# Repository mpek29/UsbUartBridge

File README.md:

# UsbUartBridge

## 🚀 Overview

**UsbUartBridge** is an open-source PCB designed to provide a **USB-to-UART bridge** for seamless serial communication between a computer and microcontrollers. The board features **JST-SH & JST-PH connectors** for easy integration into embedded projects, IoT devices, and prototyping setups.

## 🎯 Purpose

- 🔌 **Reliable USB-to-Serial Conversion**: Enables communication between a PC and embedded systems via UART.
- 📏 **Compact and Adafruit-compatible**: Designed to fit within Adafruit's standard PCB footprint.
- 🛠️ **Open-source and customizable**: Modify and adapt the design to suit your specific needs.

## 📝 Features

| 🏷️ Feature            | 🔍 Description                                                                           |
| ---------------------- | ---------------------------------------------------------------------------------------- |
| 🔌 **USB Interface**   | Micro-USB (for PC connection)                                                            |
| 📡 **UART Interface**  | TX, RX, DTR                                                                              |
| 🔋 **Voltage Options** | 3.3V & 5V selectable output                                                              |
| 🛠️ **Connectivity**   | JST-SH & JST-PH connectors for easy integration                                          |
| 🔧 **Capacitors**      | Decoupling capacitors for stability                                                      |
| 🖥️ **PCB Design**     | Open-source & customizable                                                               |
| 🌍 **Use Cases**       | Debugging & Programming microcontrollers, IoT device communication, serial data transfer |

## 📐 PCB Design Preview
| 📜 Schematic | 🖥️ PCB Layout | 🏗️ 3D |
|-----------|-----------|-----------|
|  |  |  |

## 🌟 License

This project is open-source. Feel free to use, modify, and contribute! 🚀

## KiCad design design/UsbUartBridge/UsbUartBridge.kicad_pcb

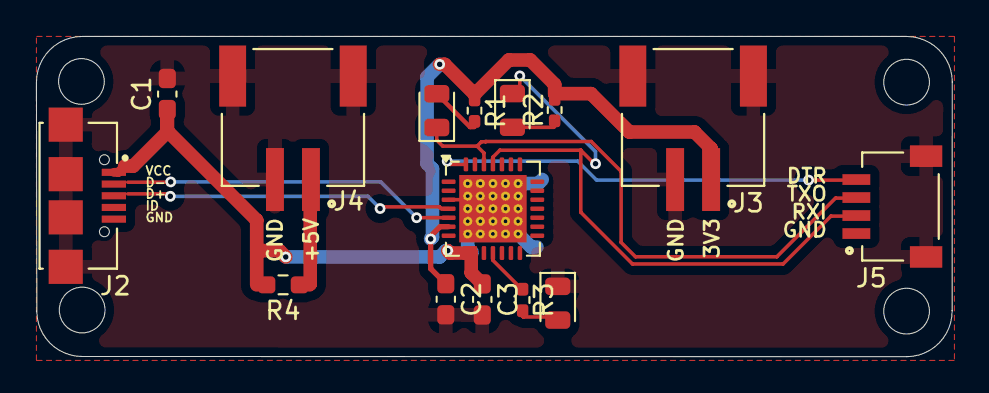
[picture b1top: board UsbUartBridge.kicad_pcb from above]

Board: 2 copper layers, 50.9 x 17.8 mm, 15 parts (0 on the bottom side), 13 nets.

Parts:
C1, C2, C3: 100nF; C_0603_1608Metric_Pad1.08x0.95mm_HandSolder
D1, D2, D3: LED; LED_0805_2012Metric
J2: UJ2-MIBH-G-SMT-TR; CUI_UJ2-MIBH-G-SMT-TR
J3, J4: S2B-PH-SM4-TB_LF__SN_; JST_S2B-PH-SM4-TB_LF__SN_
J5: SM04B-SRSS-TB_LF__SN_; JST_SM04B-SRSS-TB_LF__SN_
R1, R2, R3: 1k; R_0402_1005Metric_Pad0.72x0.64mm_HandSolder
R4: 470; R_0603_1608Metric_Pad0.98x0.95mm_HandSolder
U1: CP2102; QFN-28-1EP_5x5mm_P0.5mm_EP3.75x3.75mm_ThermalVias

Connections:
+5V: J4.1, R4.1
D+: J2.3 (D+), U1.4 (D+)
D-: J2.2 (D-), U1.5 (D-)
DTR: J5.1, U1.28 (DTR)
GND: C1.2, C2.2, C3.2, D3.1 (K), J2.5 (GND), J3.2, J3.S1 (SHIELD), J3.S2 (SHIELD), J4.2, J4.S1 (SHIELD), J4.S2 (SHIELD), J5.4, J5.S1 (SHIELD), J5.S2 (SHIELD), U1.3 (GND), U1.29 (GND)
unnamed: D1.2 (A), R1.2
unnamed: D2.2 (A), R2.1
unnamed: D3.2 (A), R3.2
RXI: D2.1 (K), J5.2, U1.25 (RXD)
TXO: D1.1 (K), J5.3, U1.26 (TXD)
VCC: C1.1, C3.1, J2.1 (VCC), R4.2, U1.8 (VBUS), U1.9 (~RST)
VDD: C2.1, J3.1, R1.1, R2.2, U1.6 (VDD)
~SUSPEND: R3.1, U1.11 (~SUSPEND)

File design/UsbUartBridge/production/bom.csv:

Designator,Footprint,Quantity,Value,LCSC Part #
"C1, C2, C3",0603,3,100nF,
"D1, D2, D3",0805,3,LED,
J2,CUI_UJ2-MIBH-G-SMT-TR,1,UJ2-MIBH-G-SMT-TR,
"J3, J4",JST_S2B-PH-SM4-TB_LF__SN_,2,S2B-PH-SM4-TB_LF__SN_,
J5,JST_SM04B-SRSS-TB_LF__SN_,1,SM04B-SRSS-TB_LF__SN_,
"R1, R2, R3",0402,3,1k,
R4,0603,1,470,
U1,QFN-28-1EP_5x5mm_P0.5mm_EP3.75x3.75mm_ThermalVias,1,CP2102,

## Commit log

2025-04-10 adjustement and gerber files
